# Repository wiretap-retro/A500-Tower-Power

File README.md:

# A500 Tower Power
A small ATX to Amiga 500 power adapter for towerized A500 builds. Includes 3 fan connectors.

## Intro
I developed this adapter for my Amiga 500 tower project. It mounts to the motherboard tray or any other convenient area inside the case via two standoffs. It allows you to plug in a standard ATX power supply and provides a 4-pin molex connector (for the A500 power connector) along with 3 standard fan headers for 12V fans. 

## Assembly / Installation
* Order the PCB from your fabricator of choice. (JLCPCB, PCBway, OSH Park, etc.) This is a 4-layer PCB, so JLCPCB will probably be cheapest.
* Order the parts per the BOM. Mouser part numbers are included. A standard 2-pin 2.54mm pin header, 3mm LED, and a standard resistor are also needed, but who doesn't have those laying around?
* Solder the J3 pin header, LED, and resistor first. Alternatively, you can put another 2x2.54mm pin header in place of the LED to use it as a front panel power LED.
* Solder the 4-pin molex, 24-pin ATX header, and the 3-pin fan headers.
* Obtain an A500 power connector either from a failed power supply or order a new connector.
* From an old ATX power supply, molex passthrough, or molex splitter, clip the leads of a 4-pin molex so you have only the female end with long leads.
* Strip and tin the leads of the 4-pin molex cable and solder them into the Amiga 500 power connector, paying close attention to pinouts of both the A500 and this power adapter board. (heatshrink the wires if necessary at this step)
* Plug the A500 to 4-pin molex dongle into the A500 Tower Power adapter.
* Mount the power adapter in a conventient location in your case, then plug in all the power connectors. The 2-pin PWR switch is for a standard toggle switch (or latching push button) for controlling the ATX power supply on/off function. I recommend swapping out the ATX case power button with a latching push button if you can find one that works for you. Alternatively, you can place a jumper on these pins and utilize the switch on the rear of the ATX power supply for on/off control.
* Power on the Amiga Tower and enjoy.

## Revision Info
* Rev 1: Moved power LED from PG over to the 5V line. The PG signal turns off after the ATX power supply tests itself, depending on the PSU. Important if you wanted to use it as a power LED on the front of the case by putting a 2-pin header there instead.
* Rev 0: Initial rev -- tested/working

## Misc
This is an open source design. Feel free to do what you want with it.

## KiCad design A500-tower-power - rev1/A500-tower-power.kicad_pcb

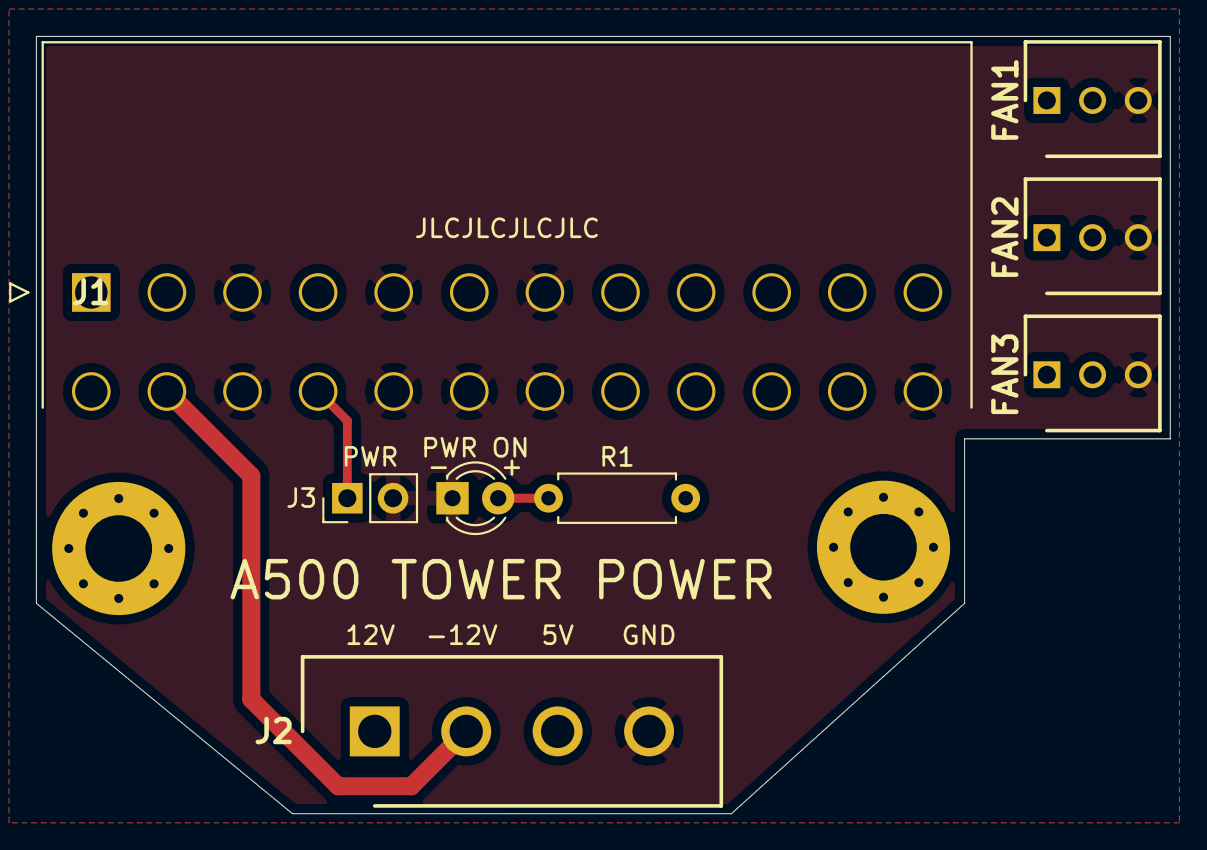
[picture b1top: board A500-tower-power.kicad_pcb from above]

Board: 4 copper layers, 63.0 x 43.2 mm, 10 parts (0 on the bottom side), 7 nets.

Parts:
D1: LED_3mm; LED_D3.0mm
FAN1, FAN2, FAN3: 22-23-2031; SHDR3W82P0X254_1X3_747X635X818P
H1, H2: MountingHole; MountingHole_3.7mm_Pad_Via
J1: 87427-2402
J2: 15-24-4449; SHDR4W166P0X508_1X4_2326X828X1066P
J3: Conn_01x02; PinHeader_1x02_P2.54mm_Vertical
R1: 1k; R_Axial_DIN0207_L6.3mm_D2.5mm_P7.62mm_Horizontal

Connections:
/3.3V: J1.1, J1.2, J1.12, J1.13
/5V: J1.4, J1.6, J1.21, J1.22, J1.23, J2.3, R1.2
/12V: FAN1.2, FAN2.2, FAN3.2, J1.10, J1.11, J2.1
/-12V: J1.14, J2.2
/GND: D1.1, FAN1.3, FAN2.3, FAN3.3, J1.3, J1.5, J1.7, J1.15, J1.17, J1.18, J1.19, J1.24, J2.4, J3.2
/PS-ON: J1.16, J3.1
unnamed: D1.2, R1.1
